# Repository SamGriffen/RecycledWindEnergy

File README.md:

# Scooterbine
Files for my recycled wind energy project.

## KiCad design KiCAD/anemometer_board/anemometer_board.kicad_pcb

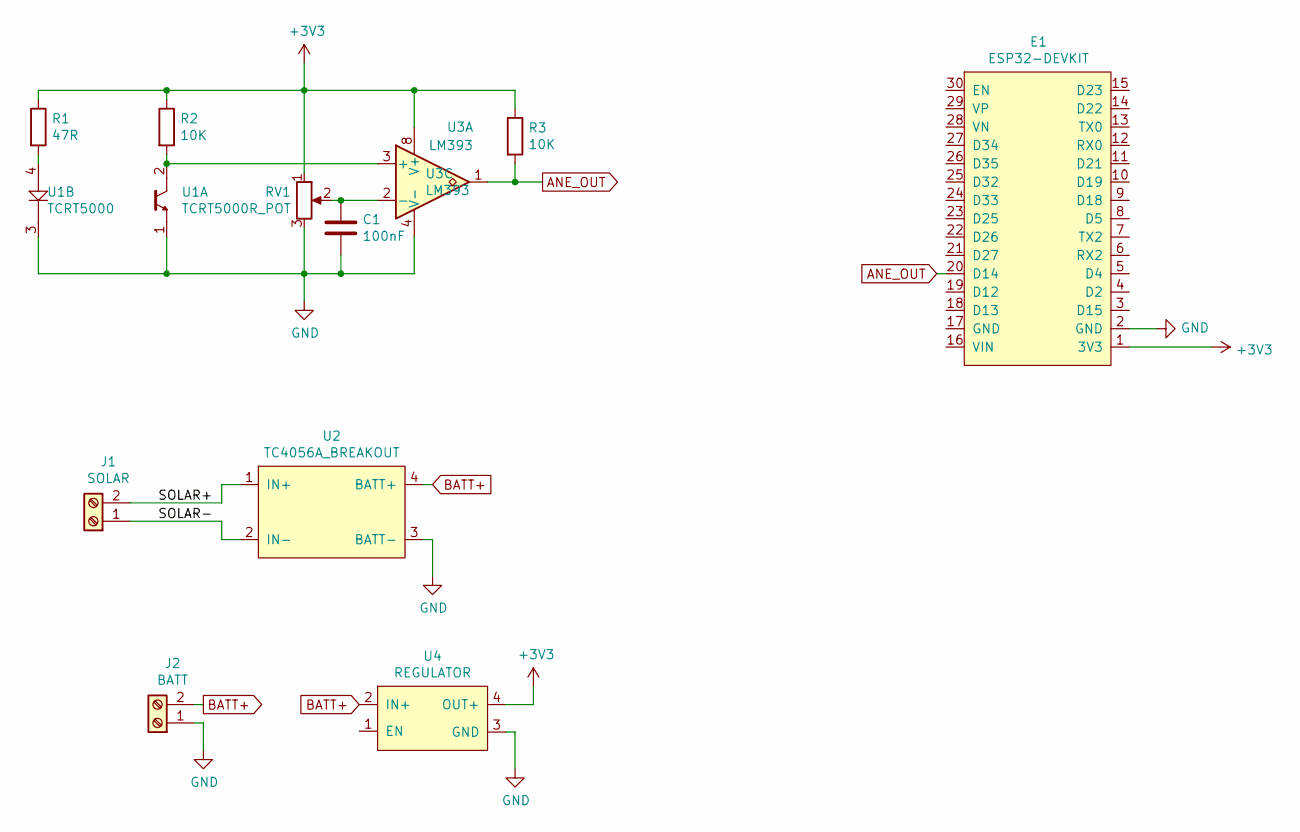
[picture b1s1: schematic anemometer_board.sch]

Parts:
C1: 100nF; C_0603_1608Metric_Pad1.05x0.95mm_HandSolder
E1: ESP32-DEVKIT; ESP31-DEVKIT
J1: SOLAR; 2_double_spaced
J2: BATT; 2_double_spaced
R1: 47R; R_Axial_DIN0204_L3.6mm_D1.6mm_P5.08mm_Horizontal
R2, R3: 10K; R_Axial_DIN0204_L3.6mm_D1.6mm_P5.08mm_Horizontal
RV1: R_POT; 3_double_spaced
U1: TCRT5000; 4x1
U2: TC4056A_BREAKOUT
U3: LM393; DIP-8_W7.62mm_Socket
U4: REGULATOR; 4x1

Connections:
+3V3: E1.1 (3V3), R1.1, R2.1, R3.1, RV1.1, U3.8 (V+), U4.4 (OUT+)
/SOLAR+: J1.2, U2.1 (IN+)
/SOLAR-: J1.1, U2.2 (IN-)
ANE_OUT: E1.20 (D14), R3.2, U3.1
BATT+: J2.2, U2.4 (BATT+), U4.2 (IN+)
GND: C1.2, E1.2 (GND), J2.1, RV1.3, U1.1, U1.3, U2.3 (BATT-), U3.4 (V-), U4.3 (GND)
unnamed: C1.1, RV1.2, U3.2 (-)
unnamed: R1.2, U1.4
unnamed: R2.2, U1.2, U3.3 (+)

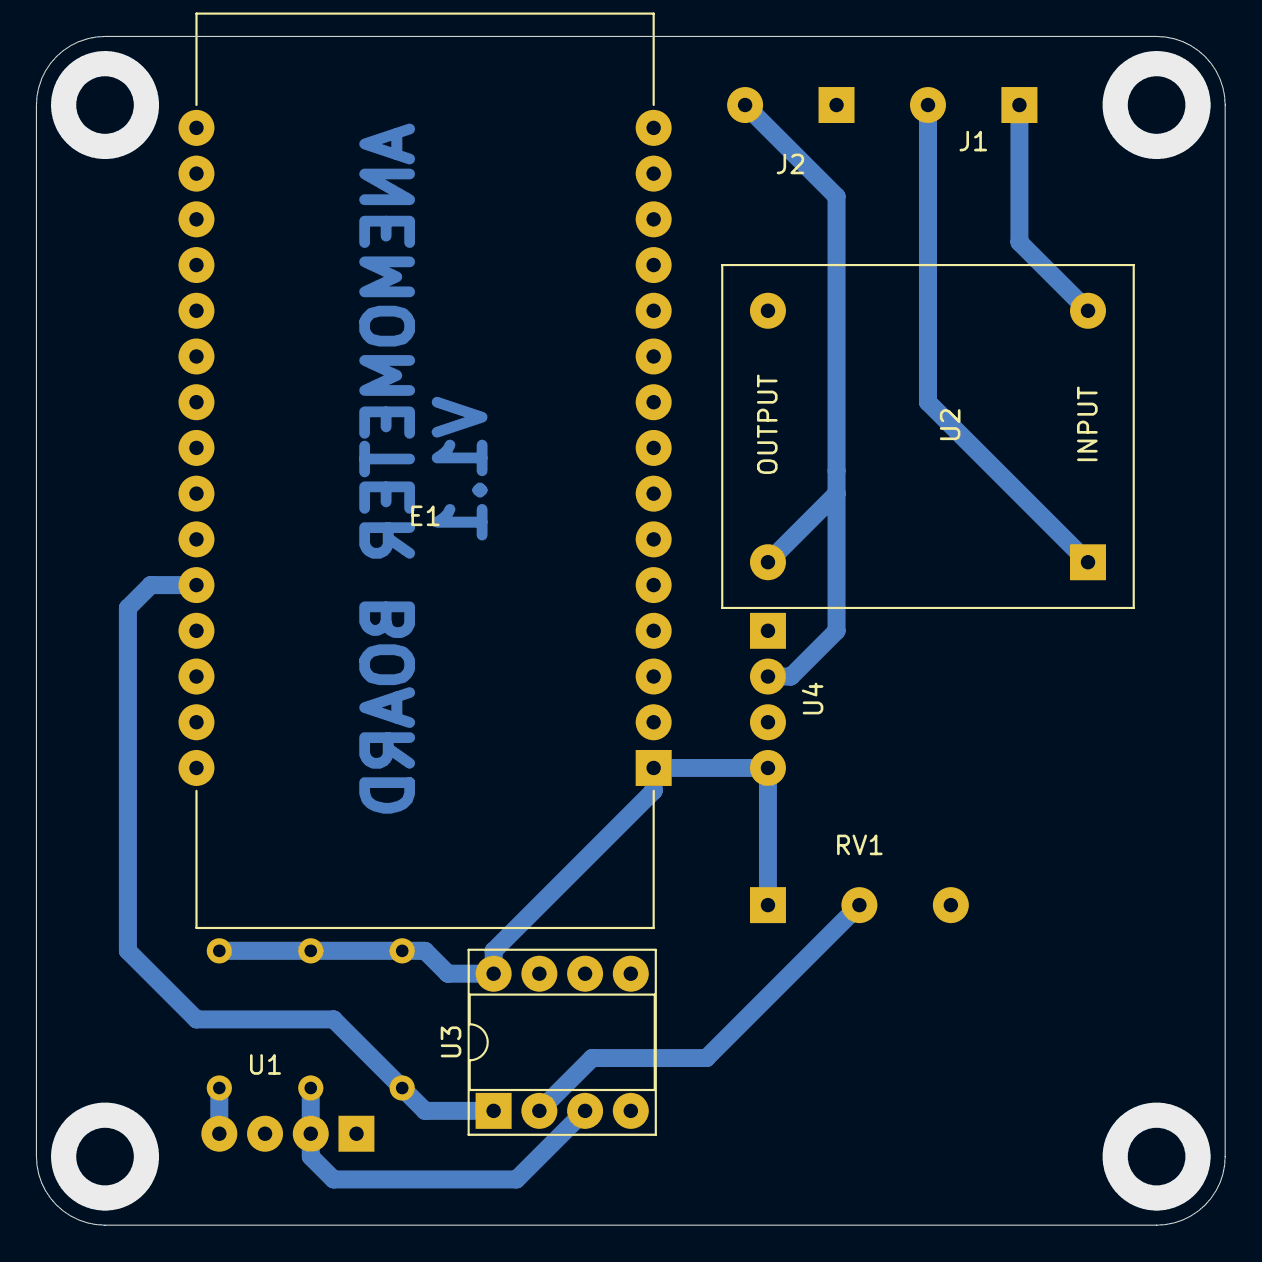
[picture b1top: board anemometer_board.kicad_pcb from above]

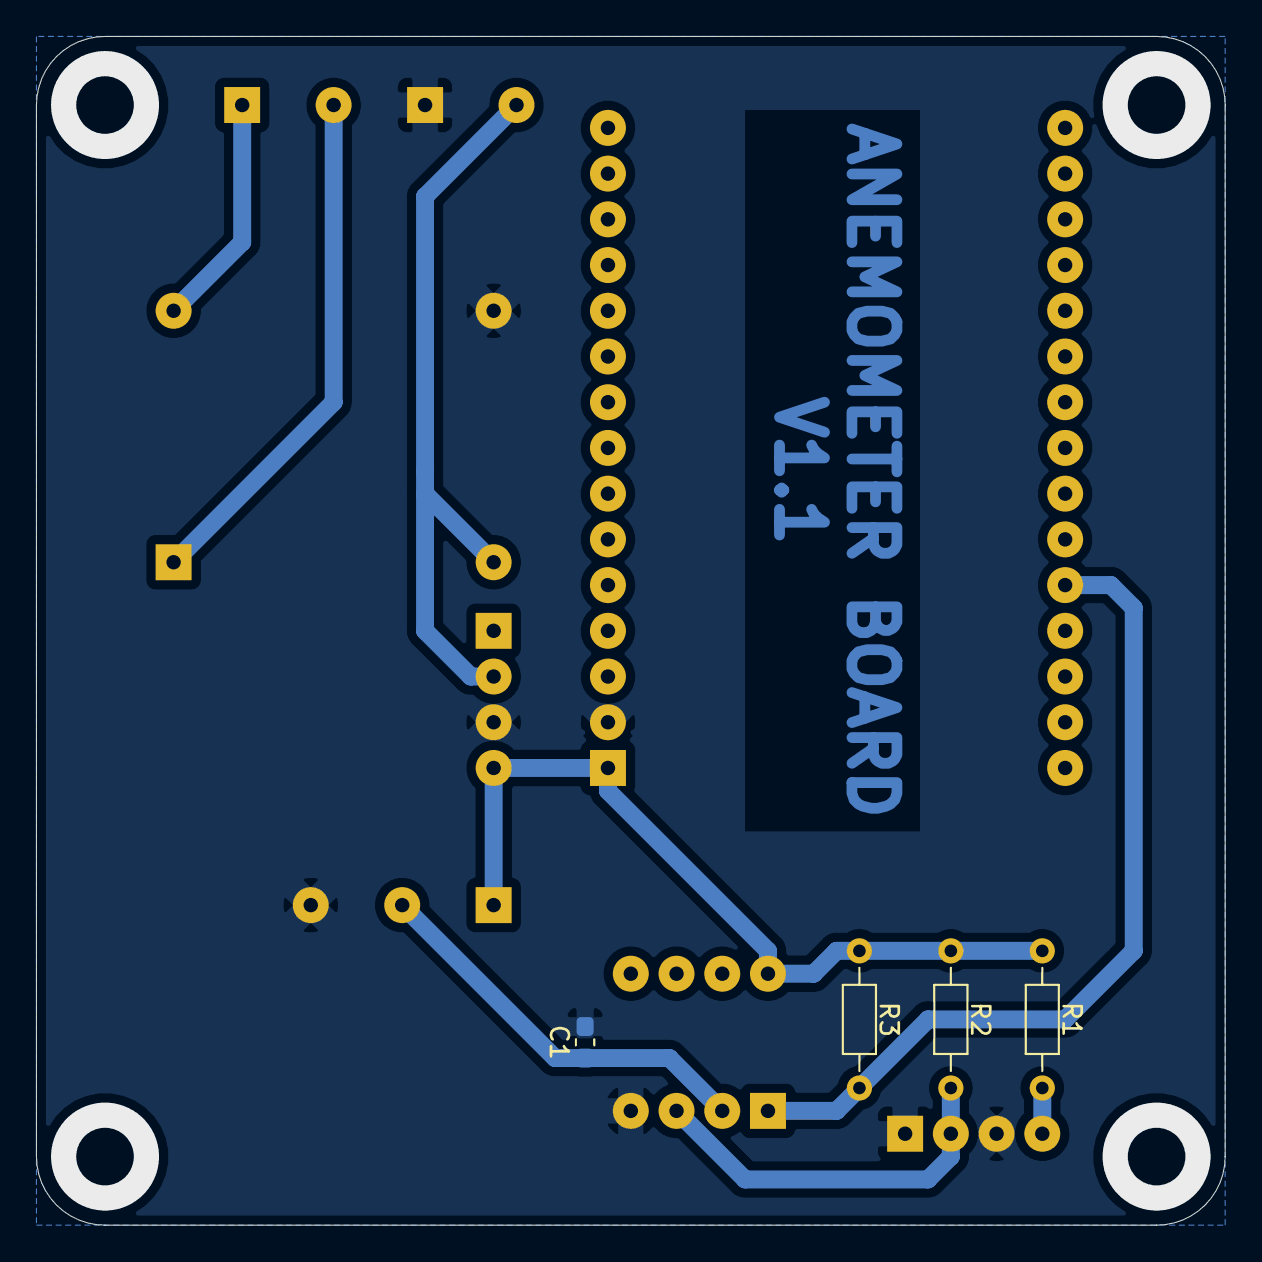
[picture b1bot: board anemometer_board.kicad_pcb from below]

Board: 2 copper layers, 66.0 x 66.0 mm, 12 parts (4 on the bottom side), 9 nets.

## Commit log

2020-12-07 Initial V1 commit. Includes anemometer code and PCB files
2020-12-07 Fix IR connections on PCB. Deploy as PCB V1.1
